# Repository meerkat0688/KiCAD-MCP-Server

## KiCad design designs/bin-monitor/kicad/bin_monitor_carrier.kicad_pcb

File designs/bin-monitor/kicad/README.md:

# 垃圾桶監視器 KiCad 載板草案

v0.3 DRAFT，2026-11-17。依使用者後續指示，先完成可編輯電路與 PCB；兩個模組目前均未持有，所有實物驗收仍未執行。

直接以 KiCad 10 開啟 [bin_monitor_carrier.kicad_pro](bin_monitor_carrier.kicad_pro)，再進入 [原理圖](bin_monitor_carrier.kicad_sch) 或 [PCB](bin_monitor_carrier.kicad_pcb)。保持整個資料夾一起移動，專案內的 BinMonitor.kicad_sym、BinMonitor.pretty 及相對 library tables 供應自訂元件。

| 項目 | 本版設計 |
|---|---|
| 板外形 | 50 × 38 mm、四角 R2、厚度 1.6 mm |
| 銅層 | 2 層；底層 GND pour；I²C 分層避交叉 |
| 固定 | 四個 2.2 mm NPTH、M2；每孔保留 5 mm 螺絲頭銅箔禁佈範圍 |
| 控制器 A1 | XIAO ESP32C3，使用兩列 7-pin 排針；USB 朝左邊緣；天線在模組上，載板沒有 RF 走線 |
| 感測器 | Pololu 3415 在板外，短線接 J1；本板不含裸 ToF 感測 IC |
| 供電 | 只由 XIAO USB-C 輸入 5 V；載板從模組取得 3.3 V；不接電池或第二電源 |
| J1 | JST XH 2.5 mm：1=3V3、2=GND、3=SDA、4=SCL |
| 狀態 LED | D2 / GPIO4 / A1 pad3 → 1k R1 → D1 anode；D1 cathode 接 GND，active high；韌體尚待實作 |
| 去耦 | J1 附近 10 µF / 10 V 0805 與 100 nF / 16 V 0603 |
| 測點 | TP1=3V3、TP2=GND、TP3=SDA、TP4=SCL；銅箔測點與孔不列採購 BOM |
| 初始設計規則 | 0.2 mm 間距、0.25 mm 訊號、0.5 mm 電源、0.6/0.3 mm via |

J1 的編號是本載板介面，不等於 Pololu 接腳由左到右的編號。感測模組端必須按 **VIN / GND / SDA / SCL 絲印**接線。VIN 維持 3.3 V，carrier I²C pull-up 會隨 VIN 改變；不可改接 5 V 後仍直連 ESP32。初版線長目標≤20 cm、100 kHz，這是設計假設，須量波形。XSHUT、GPIO1、VDD 初版不接線。

板上不額外增加 I²C 上拉，使用指定 Pololu carrier 的既有上拉。禁止以外觀相似的無位準轉換裸模組直接替換。這版沒有可宣稱通過的外接埠 ESD／長線防護驗證。

## 靜態檢查與預覽

[review/validation.json](review/validation.json) 記錄實際 KiCad 10.0.8 檢查：ERC 0、DRC 0、未佈線 0、原理圖一致性問題 0；另以匯出的 netlist 核對 21 個必要接點。使用 `--severity-all`，未以排除違規取得結果。原始報告為 [erc.json](review/erc.json) 與 [drc.json](review/drc.json)，並保存設計檔 SHA-256。

預覽：[原理圖 PNG](review/schematic.png)、[PCB 正面 PNG](review/pcb-top.png)、[PCB 背面 PNG](review/pcb-bottom.png)。正面圖不含底層走線，SCL 與部分電源線要在背面或 KiCad 層面板中查看。預覽不是製造檔。

ERC／DRC 不能證明 130 cm 感測、Wi-Fi、LINE、電源、接頭或機構通過。先前 US$43.85 是不含客製載板的模組原型規劃；新增 PCB、接頭、LED、電阻電容及組裝尚未報價，目前不能宣稱整套低於 US$50。

## 庫來源與裝配限制

模組符號與接腳中心來自 Seeed 官方 XIAO symbol／DIP footprint archives。專案衍生版本僅保留 14 個外圍接點，不使用底面電池與 JTAG 接點；排針孔改為 1.0 mm、焊盤 1.9 mm，仍須用實際排針尺寸及容差確認。保留極性方焊盤 1。刪除 vendor 封裝中不相干／非可攜的 3D model 路徑，重新安排絲印，未宣稱有經核對的 3D 組裝模型。

XIAO 以排針架高，不能把這個 THT 介面誤作直接 castellated SMD 安裝。需在 1:1 圖及實物上核對 USB 插拔、排針間距、高度、天線與固定支架。載板尺寸是為第一版評估選定，尚未由桶體安裝照片定版。Sensor 用獨立固定架朝下，不能只把本板貼在桶緣就假設光路正確。

Seeed 來源、下載 SHA-256、衍生修改及 KiCad 標準封裝副本列於 [library-provenance.json](library-provenance.json)。來源元件庫保存在 vendor-source/。新增零件的 Manufacturer、MPN 和 Datasheet 已寫入原理圖；完整裝置含板外模組的清單見 [../bom.csv](../bom.csv)。

## 重現

在 repository 根目錄、目標原理圖與 PCB 均未於 GUI 開啟時：

```bash
PYTHONNOUSERSITE=1 venv/bin/python designs/bin-monitor/kicad/prepare_libraries.py
PYTHONNOUSERSITE=1 venv/bin/python designs/bin-monitor/kicad/layout_board.py
python3 designs/bin-monitor/kicad/verify_kicad.py
```

layout_board.py 從 MCP 已由原理圖同步的 `.unrouted.kicad_pcb` 產生佈局；它會覆寫本版生成板，勿用來覆蓋手動修改。verify_kicad.py 執行 refill／save 與檢查，也應在 GUI 未持有目標檔時執行。上述腳本路徑適用目前這台 Mac。沒有輸出 Gerber、drill、貼片座標或製造 BOM；沒有採購、送板或製造放行。

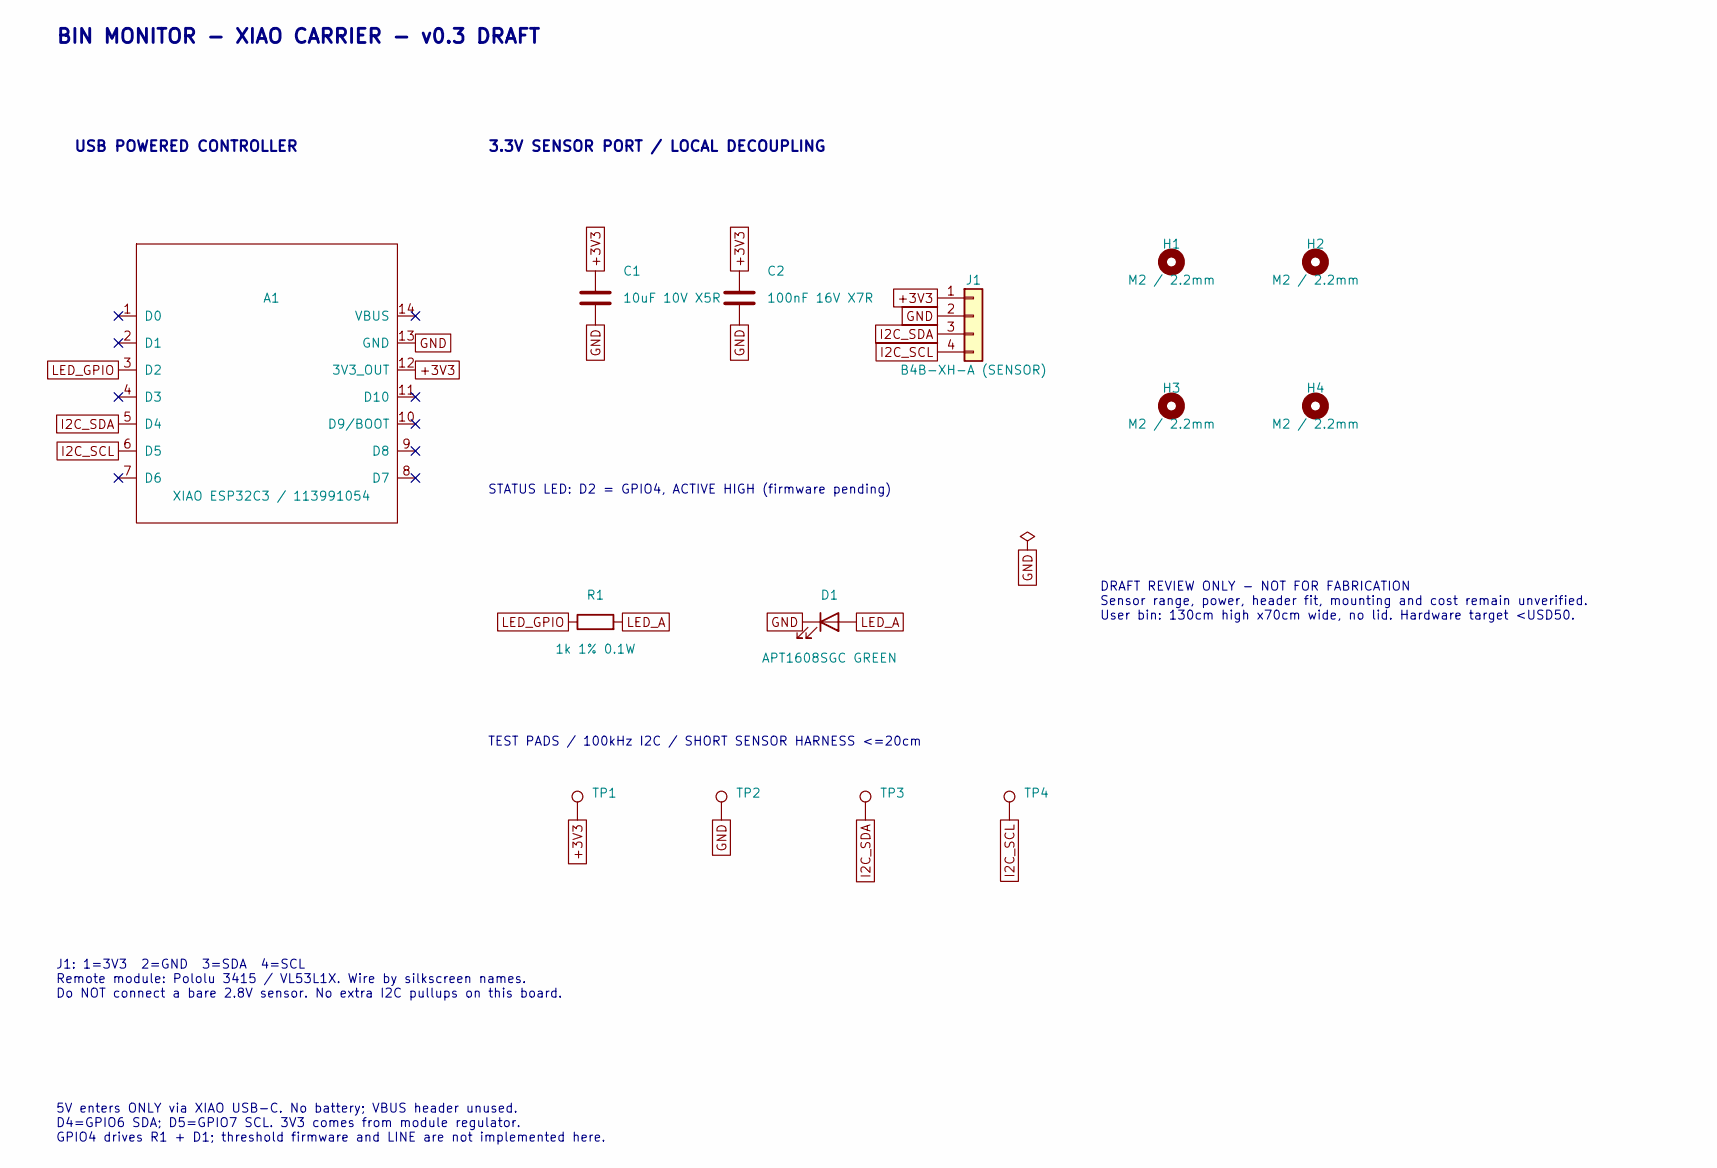
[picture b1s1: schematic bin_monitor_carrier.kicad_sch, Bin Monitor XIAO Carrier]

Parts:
A1: XIAO ESP32C3 / 113991054; XIAO_ESP32C3_14P_THT; MPN 113991054
C1: 10uF 10V X5R; C0805; MPN C2012X5R1A106K085AB
C2: 100nF 16V X7R; C0603; MPN GRM188R71C104KA01D
D1: APT1608SGC GREEN; LED0603; MPN APT1608SGC
H1, H2, H3, H4: M2 / 2.2mm; M2_Hole
J1: B4B-XH-A (SENSOR); JST_XH_1x04; MPN B4B-XH-A(LF)(SN)
R1: 1k 1% 0.1W; R0603; MPN RC0603FR-071KL
TP1: 3V3; TestPad_1p5
TP2: GND; TestPad_1p5
TP3: SDA; TestPad_1p5
TP4: SCL; TestPad_1p5

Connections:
+3V3: A1.12 (3V3_OUT), C1.1, C2.1, J1.1, TP1.1
GND: A1.13 (GND), C1.2, C2.2, D1.1 (K), J1.2, TP2.1
I2C_SCL: A1.6 (D5), J1.4, TP4.1
I2C_SDA: A1.5 (D4), J1.3, TP3.1
LED_A: D1.2 (A), R1.2
LED_GPIO: A1.3 (D2), R1.1

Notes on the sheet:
BIN MONITOR - XIAO CARRIER - v0.3 DRAFT
USB POWERED CONTROLLER
3.3V SENSOR PORT / LOCAL DECOUPLING
STATUS LED: D2 = GPIO4, ACTIVE HIGH (firmware pending)
TEST PADS / 100kHz I2C / SHORT SENSOR HARNESS <=20cm
J1: 1=3V3 2=GND 3=SDA 4=SCL Remote module: Pololu 3415 / VL53L1X. Wire by silkscreen names. Do NOT connect a bare 2.8V sensor. No extra I2C pullups on this board.
5V enters ONLY via XIAO USB-C. No battery; VBUS header unused. D4=GPIO6 SDA; D5=GPIO7 SCL. 3V3 comes from module regulator. GPIO4 drives R1 + D1; threshold firmware and LINE are not implemented here.
DRAFT REVIEW ONLY - NOT FOR FABRICATION Sensor range, power, header fit, mounting and cost remain unverified. User bin: 130cm high x70cm wide, no lid. Hardware target <USD50.

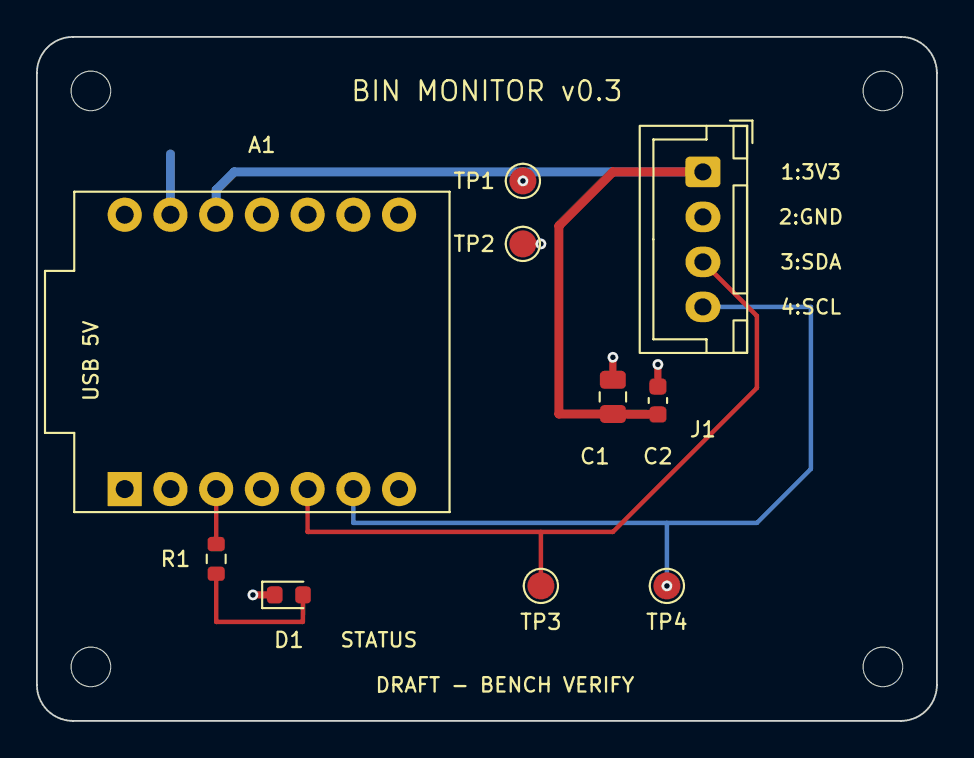
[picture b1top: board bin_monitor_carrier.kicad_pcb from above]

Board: 2 copper layers, 50.0 x 38.0 mm, 14 parts (0 on the bottom side), 6 nets.

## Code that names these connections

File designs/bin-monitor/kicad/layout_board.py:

"""Rebuild the review layout from the MCP-synchronised unrouted board.

KiCad must not have this target board open during generation. No fabrication
outputs are produced. Run KiCad CLI DRC with refill/save after this script.
"""
from pathlib import Path
import json
import math
import pcbnew as p

ROOT = Path(__file__).resolve().parent
board = p.LoadBoard(str(ROOT/'bin_monitor_carrier.unrouted.kicad_pcb'))
mm = p.FromMM
vec = lambda xy: p.VECTOR2I(mm(xy[0]), mm(xy[1]))

placement = {
    'A1':(112.5,117.5,180), 'J1':(137,107.5,270),
    'C1':(132,120,90), 'C2':(134.5,120.2,90),
    'R1':(109.96,129,270), 'D1':(114,131,0),
    'TP1':(127,108,0), 'TP2':(127,111.5,0),
    'TP3':(128,130.5,0), 'TP4':(135,130.5,0),
    'H1':(103,103,0), 'H2':(147,103,0),
    'H3':(103,135,0), 'H4':(147,135,0),
}
fps = {fp.GetReference():fp for fp in board.GetFootprints()}
assert set(fps) == set(placement), (set(fps), set(placement))
for ref,(x,y,rotation) in placement.items():
    fp=fps[ref]
    fp.SetPosition(vec((x,y)))
    fp.SetOrientationDegrees(rotation)
    fp.Value().SetVisible(False)
    fp.Reference().SetTextSize(vec((0.85,0.85)))
    fp.Reference().SetTextThickness(mm(0.13))
    fp.Reference().SetTextAngle(p.EDA_ANGLE(0,p.DEGREES_T))
    fp.Reference().SetPosition(vec((x,y-2)))
    if ref.startswith(('TP','H')):
        fp.SetExcludedFromBOM(True)
        fp.SetExcludedFromPosFiles(True)
    if ref=='A1':
        for graphic in fp.GraphicalItems():
            if graphic.GetLayer()==p.F_SilkS:
                graphic.SetLayer(p.F_Fab)

def pad(ref, number):
    return next(x for x in fps[ref].Pads() if x.GetNumber()==str(number))

def pos(ref, number):
    xy=pad(ref,number).GetPosition()
    return (p.ToMM(xy.x),p.ToMM(xy.y))

def segment(net, points, layer='F.Cu', width=0.25):
    code=board.FindNet(net).GetNetCode()
    for a,b in zip(points,points[1:]):
        if a==b: continue
        track=p.PCB_TRACK(board)
        track.SetStart(vec(a)); track.SetEnd(vec(b))
        track.SetLayer(board.GetLayerID(layer)); track.SetWidth(mm(width)); track.SetNetCode(code)
        board.Add(track)

def via(net, xy):
    item=p.PCB_VIA(board)
    item.SetPosition(vec(xy)); item.SetWidth(mm(0.6)); item.SetDrill(mm(0.3))
    item.SetViaType(p.VIATYPE_THROUGH); item.SetLayerPair(p.F_Cu,p.B_Cu)
    item.SetNetCode(board.FindNet(net).GetNetCode()); board.Add(item)

# Assert the electrical intent before adding any copper.
expected = {
    ('A1','3'):'LED_GPIO', ('A1','5'):'I2C_SDA', ('A1','6'):'I2C_SCL',
    ('A1','12'):'+3V3', ('A1','13'):'GND',
    ('J1','1'):'+3V3', ('J1','2'):'GND', ('J1','3'):'I2C_SDA', ('J1','4'):'I2C_SCL',
    ('C1','1'):'+3V3', ('C1','2'):'GND', ('C2','1'):'+3V3', ('C2','2'):'GND',
    ('R1','1'):'LED_GPIO', ('R1','2'):'LED_A', ('D1','2'):'LED_A', ('D1','1'):'GND',
    ('TP1','1'):'+3V3', ('TP2','1'):'GND', ('TP3','1'):'I2C_SDA', ('TP4','1'):'I2C_SCL',
}
for key,net in expected.items():
    assert pad(*key).GetNetname()==net, (key,pad(*key).GetNetname(),net)

# Sensor power: bottom-layer distribution, front decoupling next to connector.
segment('+3V3',[pos('A1',12),(109.96,108.5),(110.96,107.5),pos('J1',1)],'B.Cu',0.5)
segment('+3V3',[(127,107.5),(127,108)],'B.Cu',0.4)
via('+3V3',(127,108))
segment('+3V3',[pos('J1',1),(132,107.5),(129,110.5),(129,120.95),pos('C1',1),pos('C2',1)],'F.Cu',0.5)

# Keep the two I2C traces on separate layers at their crossing.
segment('I2C_SDA',[pos('A1',5),(115.04,127.5),(132,127.5),(140,119.5),(140,115.5),pos('J1',3)])
segment('I2C_SDA',[(128,127.5),pos('TP3',1)])
segment('I2C_SCL',[pos('A1',6),(117.58,127),(140,127),(143,124),(143,115),pos('J1',4)],'B.Cu')
segment('I2C_SCL',[(135,127),pos('TP4',1)],'B.Cu')
via('I2C_SCL',pos('TP4',1))

# Low-current, active-high LED on D2/GPIO4. R1 limits current to <=3.3mA
# even for a hypothetical zero-forward-drop LED at nominal3.3V.
segment('LED_GPIO',[pos('A1',3),pos('R1',1)])
segment('LED_A',[pos('R1',2),(109.96,132.5),(114.775,132.5),pos('D1',2)])

# Local returns connect into B.Cu ground; module ground exits the zone keepout.
segment('GND',[pos('A1',13),(107.42,106.5)],'B.Cu',0.5)
for ref,number,xy in [('C1',2,(132,117.8)),('C2',2,(134.5,118.2)),('D1',1,(112,131)),('TP2',1,(128,111.5))]:
    segment('GND',[pos(ref,number),xy],width=0.4)
    via('GND',xy)

zone=p.ZONE(board)
zone.SetLayer(p.B_Cu); zone.SetNetCode(board.FindNet('GND').GetNetCode())
zone.SetLocalClearance(mm(0.25)); zone.SetThermalReliefGap(mm(0.3))
zone.SetThermalReliefSpokeWidth(mm(0.3)); zone.SetMinThickness(mm(0.2))
zone.Outline().NewOutline()
for xy in [(100.6,100.6),(149.4,100.6),(149.4,137.4),(100.6,137.4)]:
    zone.Outline().Append(int(mm(xy[0])),int(mm(xy[1])))
board.Add(zone)

# No zone copper beneath the module; tracks are explicitly allowed.
keep=p.ZONE(board); keep.SetIsRuleArea(True)
layers=p.LSET(); layers.AddLayer(p.F_Cu); layers.AddLayer(p.B_Cu)
keep.SetLayerSet(layers)
keep.SetDoNotAllowZoneFills(True); keep.SetDoNotAllowTracks(False)
keep.SetDoNotAllowVias(False); keep.SetDoNotAllowPads(False); keep.SetDoNotAllowFootprints(False)
keep.SetZoneName('XIAO_BODY_NO_ZONE_COPPER')
keep.Outline().NewOutline()
for xy in [(101.7,108.3),(123.5,108.3),(123.5,127.7),(101.7,127.7)]:
    keep.Outline().Append(int(mm(xy[0])),int(mm(xy[1])))
board.Add(keep)

# Reserve a 5mm screw-head envelope at every M2 mounting position.
for ref in ['H1','H2','H3','H4']:
    hole_keep=p.ZONE(board); hole_keep.SetIsRuleArea(True)
    hole_keep.SetLayerSet(layers); hole_keep.SetDoNotAllowZoneFills(True)
    hole_keep.SetDoNotAllowTracks(True); hole_keep.SetDoNotAllowVias(True)
    hole_keep.SetDoNotAllowPads(False); hole_keep.SetDoNotAllowFootprints(False)
    hole_keep.SetZoneName(ref+'_M2_SCREW_CLEARANCE')
    hole_keep.Outline().NewOutline()
    x,y,_=placement[ref]
    for i in range(32):
        angle=2*math.pi*i/32
        hole_keep.Outline().Append(int(mm(x+2.5*math.cos(angle))),int(mm(y+2.5*math.sin(angle))))
    board.Add(hole_keep)

def text(content,xy,size=0.9,layer=p.F_SilkS,rotation=0):
    item=p.PCB_TEXT(board); item.SetText(content); item.SetPosition(vec(xy))
    item.SetTextSize(vec((size,size))); item.SetTextThickness(mm(0.13))
    item.SetLayer(layer); item.SetTextAngle(p.EDA_ANGLE(rotation,p.DEGREES_T)); board.Add(item)
    if layer in (p.B_Fab,p.B_SilkS): item.SetMirrored(True)

# Compact, meaningful on-board annotations.
def silk_line(a,b):
    shape=p.PCB_SHAPE(board); shape.SetShape(p.SHAPE_T_SEGMENT)
    shape.SetStart(vec(a)); shape.SetEnd(vec(b)); shape.SetLayer(p.F_SilkS)
    shape.SetWidth(mm(0.12)); board.Add(shape)
for a,b in [((102.075,108.6),(122.925,108.6)),((122.925,108.6),(122.925,126.4)),
            ((122.925,126.4),(102.075,126.4)),((102.075,126.4),(102.075,122)),
            ((102.075,113),(102.075,108.6)),((102.075,113),(100.45,113)),
            ((100.45,113),(100.45,122)),((100.45,122),(102.075,122))]:
    silk_line(a,b)
for ref,xy in {'A1':(112.5,106),'J1':(137,121.8),'C1':(131,123.3),'C2':(134.5,123.3),
               'R1':(107.7,129),'D1':(114,133.5),
               'TP1':(124.3,108),'TP2':(124.3,111.5),
               'TP3':(128,132.5),'TP4':(135,132.5)}.items():
    fps[ref].Reference().SetPosition(vec(xy))
for ref in ['H1','H2','H3','H4']:
    fps[ref].Reference().SetVisible(False)
text('BIN MONITOR v0.3',(125,103),1.1)
text('DRAFT - BENCH VERIFY',(126,136),0.8)
text('USB 5V',(103,118),0.8,rotation=90)
for label,y in [('1:3V3',107.5),('2:GND',110),('3:SDA',112.5),('4:SCL',115)]:
    text(label,(143, y),0.8)
text('STATUS',(119,133.5),0.8)
text('50x38mm / 2 layer / 1.6mm',(125,119),1.0,layer=p.B_Fab)
text('DRAFT ONLY - NO FAB RELEASE',(125,122),0.8,layer=p.B_Fab)

board.SetCopperLayerCount(2)
board.GetDesignSettings().SetBoardThickness(mm(1.6))
board.GetTitleBlock().SetTitle('Bin Monitor XIAO Carrier')
board.GetTitleBlock().SetRevision('v0.3 DRAFT')
board.GetTitleBlock().SetDate('2026-11-17')
p.SaveBoard(str(ROOT/'bin_monitor_carrier.kicad_pcb'),board)
manifest={
    'board_mm':{'x':100,'y':100,'width':50,'height':38,'corner_radius':2,'thickness':1.6},
    'layers':2,'placement':placement,'pad_nets':{f'{ref}.{number}':net for (ref,number),net in expected.items()},
    'tracks':len(list(board.GetTracks())), 'ground_zone':'B.Cu',
    'physical_validation':'NOT RUN','fabrication_release':False,
}
(ROOT/'layout-manifest.json').write_text(json.dumps(manifest,indent=2)+'\n')
print('Saved review board:14 footprints, fully planned routes; CLI refill/DRC still required.')
for ref in ['A1','J1','C1','C2','R1','D1']:
    print(ref,{pad.GetNumber():[round(p.ToMM(pad.GetPosition().x),3),round(p.ToMM(pad.GetPosition().y),3),pad.GetNetname()] for pad in fps[ref].Pads()})
